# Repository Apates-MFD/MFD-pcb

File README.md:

# MFD-pcb

kicad project and components information of pcb

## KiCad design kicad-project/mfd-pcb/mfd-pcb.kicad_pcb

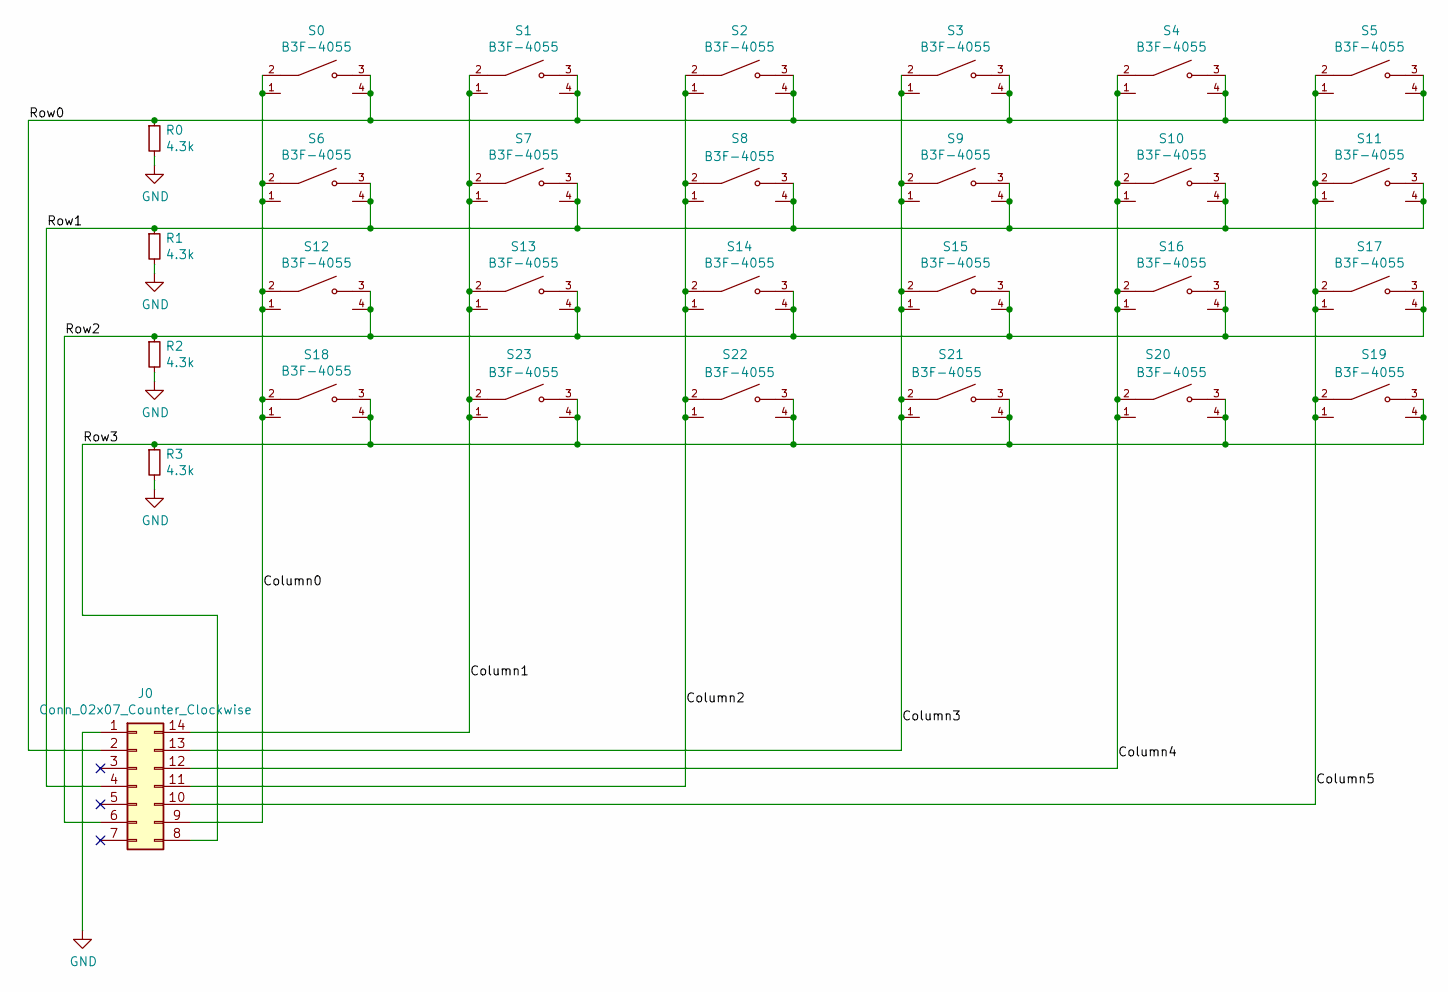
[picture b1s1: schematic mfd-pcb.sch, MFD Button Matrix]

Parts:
J0: Conn_02x07_Counter_Clockwise; PinHeader_2x07_P2.54mm_Vertical
R0, R1, R2, R3: 4.3k; R_Axial_DIN0207_L6.3mm_D2.5mm_P10.16mm_Horizontal
S0, S1, S2, S3, S4, S5, S6, S7, S8, S9, S10, S11, S12, S13, S14, S15, S16, S17, S18, S19, S20, S21, S22, S23: B3F-4055; SW_B3F-4055; PARTREV A070-E1-08

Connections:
/Column0: J0.9, S0.1, S0.2, S6.1, S6.2, S12.1, S12.2, S18.1, S18.2
/Column1: J0.14, S1.1, S1.2, S7.1, S7.2, S13.1, S13.2, S23.1, S23.2
/Column2: J0.11, S2.1, S2.2, S8.1, S8.2, S14.1, S14.2, S22.1, S22.2
/Column3: J0.13, S3.1, S3.2, S9.1, S9.2, S15.1, S15.2, S21.1, S21.2
/Column4: J0.12, S4.1, S4.2, S10.1, S10.2, S16.1, S16.2, S20.1, S20.2
/Column5: J0.10, S5.1, S5.2, S11.1, S11.2, S17.1, S17.2, S19.1, S19.2
/Row0: J0.2, R0.1, S0.3, S0.4, S1.3, S1.4, S2.3, S2.4, S3.3, S3.4, S4.3, S4.4, S5.3, S5.4
/Row1: J0.4, R1.1, S6.3, S6.4, S7.3, S7.4, S8.3, S8.4, S9.3, S9.4, S10.3, S10.4, S11.3, S11.4
/Row2: J0.6, R2.1, S12.3, S12.4, S13.3, S13.4, S14.3, S14.4, S15.3, S15.4, S16.3, S16.4, S17.3, S17.4
/Row3: J0.8, R3.1, S18.3, S18.4, S19.3, S19.4, S20.3, S20.4, S21.3, S21.4, S22.3, S22.4, S23.3, S23.4
GND: J0.1, R0.2, R1.2, R2.2, R3.2

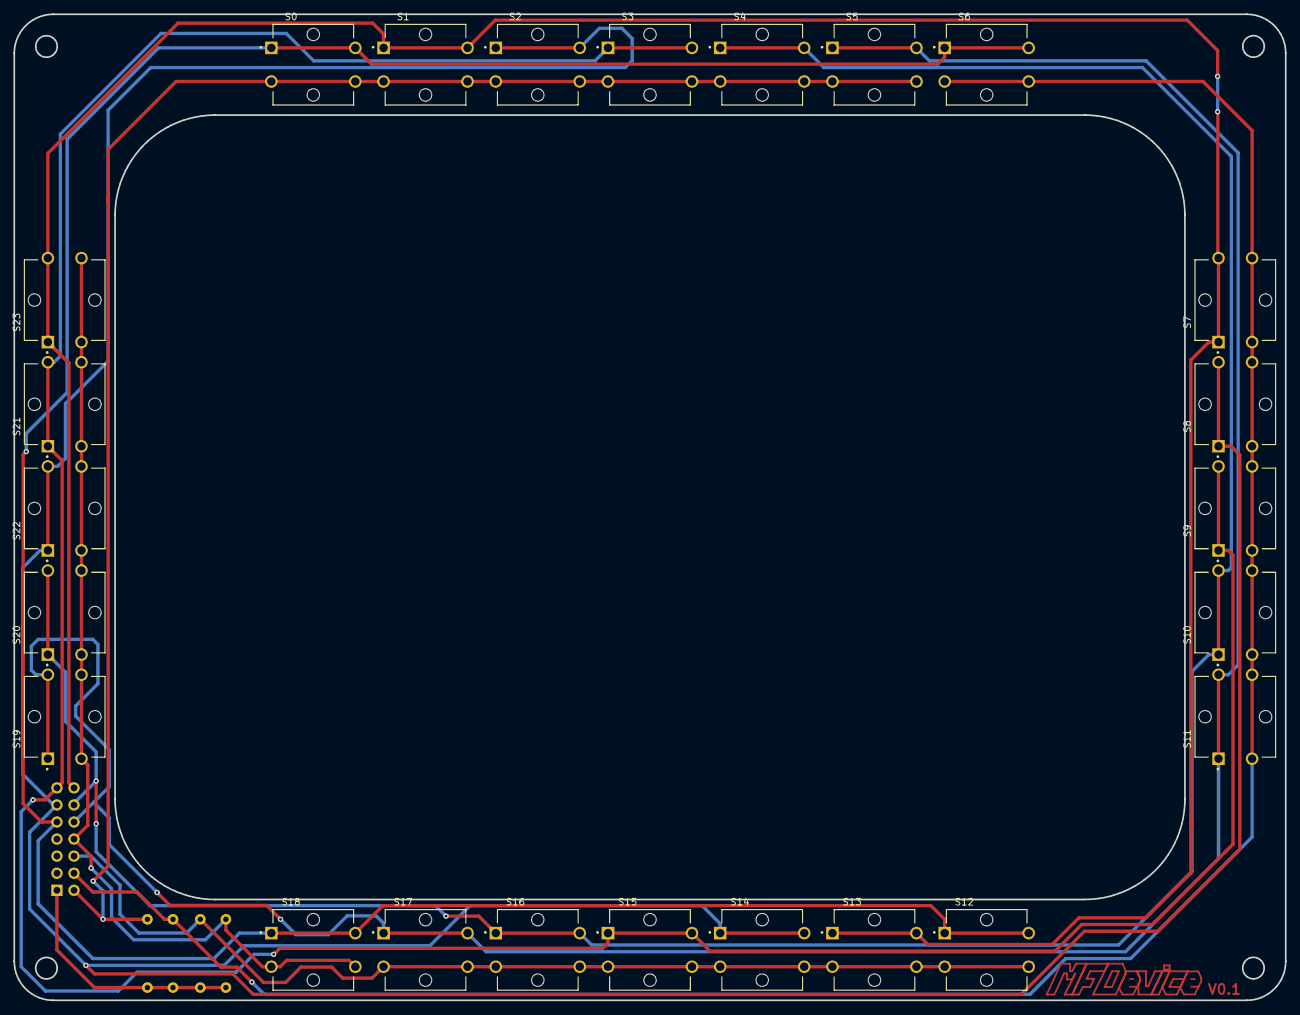
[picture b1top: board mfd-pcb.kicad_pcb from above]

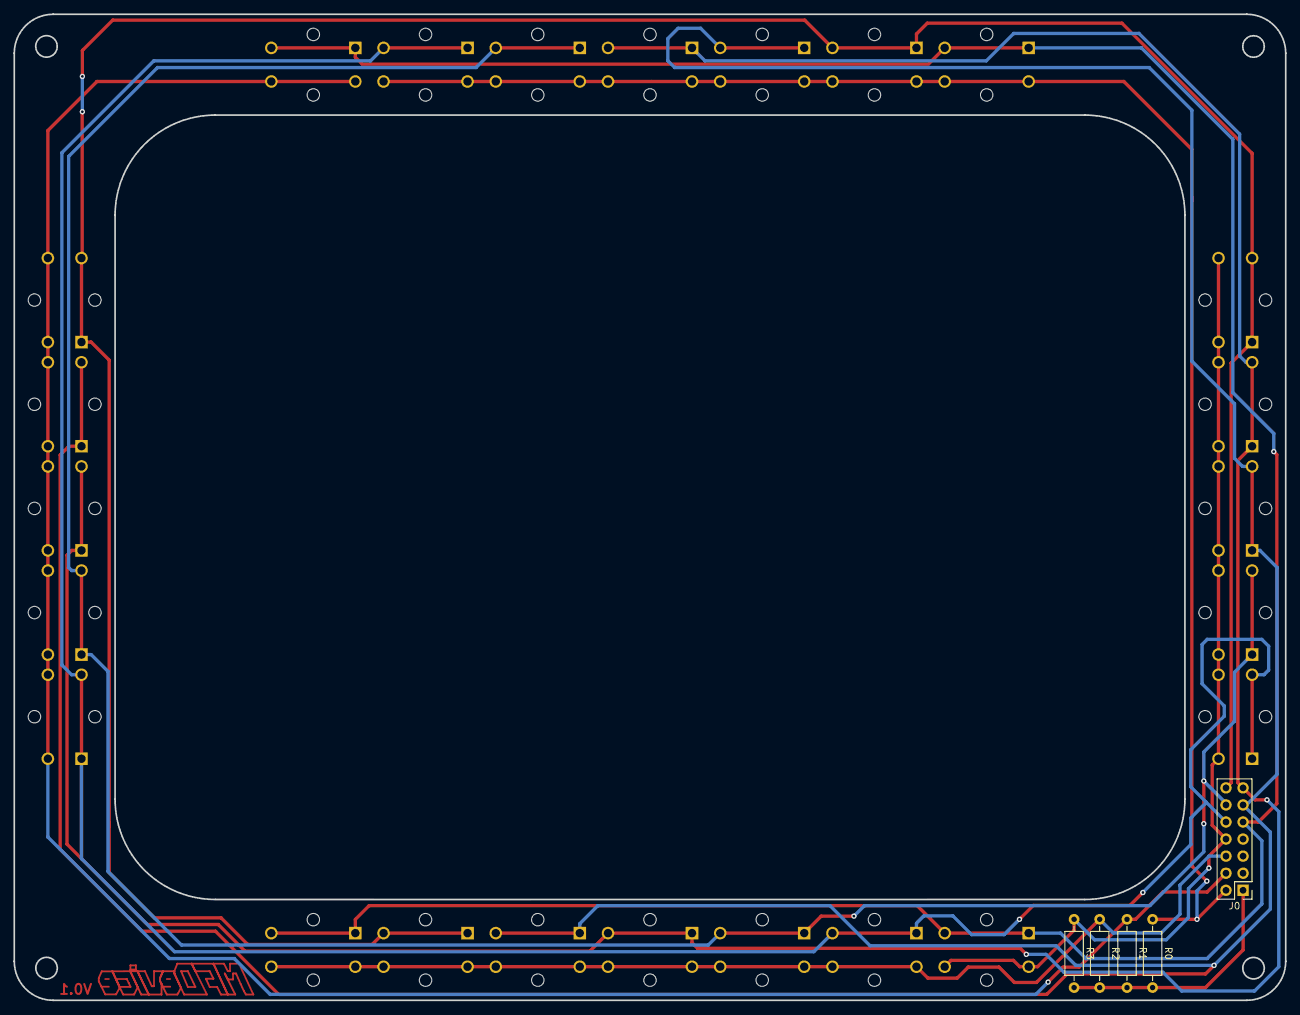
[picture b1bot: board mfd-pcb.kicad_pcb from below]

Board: 2 copper layers, 189.2 x 146.7 mm, 29 parts (5 on the bottom side), 11 nets.

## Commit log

2021-01-28 Create LICENSE
